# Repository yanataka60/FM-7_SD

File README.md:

# FM-7にSD-CARDからロード、セーブ機能

　FM-8、FM-7、FM-77シリーズでSD-CARDからロード、セーブ機能を実現するものです。

　対応できるBASICのバージョンは、FM-8はF-BASICV1.0(ROM-BASIC、DISK-VERSIONとも)、FM-7以降はF-BASICV3.0(ROM-BASIC、DISK-VERSIONとも)です。

　対応機種はFM-8からFM-77AV40SXまで全てのFMシリーズとなりますが、基板のRevsionにより対応範囲が異なります。

　Rev1.1とRev2.0の違いはコネクタのみです。

　Rev1.1はFM-7、FM-NEW7なら50Pinフラットケーブルで接続できますが、FM-77以降は外部拡張インタフェースの仕様が変更となっており、アンフェノール フルピッチへ変換するケーブルの自作が必要です。

　Rev2.0は32Pin拡張スロット仕様でFM-7以降全ての機種に接続できますが、純正の32Pinコネクタ(FCN-365P032-AU)は製造が終了してしまったため入手困難です。手持ちにある方は利用できますが、無い方はOMRON XC5A-3282-1が代替品として使えますが、加工が必要です。

　FM-8に繋げることが出来るのはRev3.0のみです。また、Rev3.0はFM-8、FM-7、FM-NEW7なら50Pinフラットケーブルで接続できますが、FM-77は外部拡張インタフェースの仕様が変更となっており、アンフェノール フルピッチへ変換するケーブルの自作が必要です。

|Revsion|対応機種|基板側コネクタ|本体側コネクタ|備考|
| ------------ | ------------ | ------------ | ------------ | ------------ |
|Rev1.1|FM-7、FM-NEW7|フラットケーブルコネクタ 50ピン|同左||
|Rev1.1|FM-77|フラットケーブルコネクタ 50ピン|アンフェノール フルピッチ50Pin|ケーブルの自作が必要|
|Rev1.1|FM-77AV|フラットケーブルコネクタ 50ピン|アンフェノール フルピッチ36Pin|ケーブルの自作が必要|
|Rev1.1|FM-77AV20以降|フラットケーブルコネクタ 50ピン|アンフェノール フルピッチ50Pin|ケーブルの自作が必要|
|Rev2.0|FM-7以降のすべて|32Pin拡張スロット||コネクタの加工が必要|
|Rev3.0|FM-8、FM-7、FM-NEW7|フラットケーブルコネクタ 50ピン|同左||
|Rev3.0|FM-77|フラットケーブルコネクタ 50ピン|アンフェノール フルピッチ50Pin|ケーブルの自作が必要|

### FM-8、FM-7、FM-77で使うときはBOOT-ROMの差替え有無を選択します。FM-77以降はFDD標準搭載なのでFDからFM-7_SD初期設定プログラムを走らせるものとしています。

　　1)BOOT-ROMを差し替える

　　2)BOOT-ROMを差し替えない。電源投入時又はRESET時に毎回CMTからFM-7_SD初期設定プログラムを読み込む(約15秒)

　　3)BOOT-ROMを差し替えない。電源投入時又はRESET時に毎回FDからFM-7_SD初期設定プログラムを走らせる。

　対応しているCMT形式は、FM-7がCMTで読み書きするベタCMT形式(拡張子bimとしています)です。T77からbimへの変換、bimからT77への変換にはツールを使って変換します。

　CMTからの読み込み実行に数分掛かっていたゲームも数十秒で実行できます。

　なお、Arduino、ROMへ書き込むための機器が別途必要となります。

## 対応できないもの
　BIOSのCMT読み書きルーチンをフックすることでSD-CARDへのアクセスを実現していますのでBIOSをコールせず独自ルーチンでCMTからLOADするソフト（ちゃっくんぽっぷ等）は対応できないのでLOAD出来ません。

　市販ソフトの多くが独自ルーチン、特殊フォーマットを使っているようです。

　bugfire2009さんのDumpListEditorにドロップしたときにファイルの大きさに比べて異様に小さなファイルしか解析できなかったり、(DAT)(unknown)と表示されるファイルが解析されるT77ファイルは独自ルーチン、特殊フォーマットを採用していると思います。

　市販ソフトがLOAD出来ればラッキーくらいに思って雑誌打ち込み系のLOADに活用してください。

## 回路図
### FM-7_SD Rev1.1基板
　KiCadフォルダ内Rev1.1フォルダのFM-7_SD_11.pdfを参照してください。

[回路図Rev1.1](https://github.com/yanataka60/FM-7_SD/blob/main/KiCad/Rev1.1/FM-7_SD_11.pdf)

### FM-7_SD Rev2.0基板
　KiCadフォルダ内Rev2.0フォルダのFM-7_SD_20.pdfを参照してください。

[回路図Rev2.0](https://github.com/yanataka60/FM-7_SD/blob/main/KiCad/Rev2.0/FM-7_SD_20.pdf)

### FM-7_SD Rev3.0基板
　KiCadフォルダ内Rev3.0フォルダのFM-7_SD_30.pdfを参照してください。

[回路図Rev3.0](https://github.com/yanataka60/FM-7_SD/blob/main/KiCad/Rev3.0/FM-7_SD_30.pdf)

## 部品
### FM-7_SD Rev1.1基板
|番号|品名|数量|備考|
| ------------ | ------------ | ------------ | ------------ |
|J1|2x25ボックスヘッダ|1|共立エレショップ JS-1200R-50など、秋月電子通商 PH-2x40RGなどのピンヘッダでも代用可(注5)|
||J4、J5のいずれか(注1)|||
|J4|Micro_SD_Card_Kit|1|秋月電子通商 AE-microSD-LLCNV (注2)|
|J5|MicroSD Card Adapter|1|Arduino等に使われる5V電源に対応したもの (注6)|
|U1|74LS04|1||
|U2|74LS30|1||
|U3|8255|1||
|U4|Arduino_Pro_Mini_5V|1|Atmega328版を使用 168版は不可。(注3)|
|U5|74LS00|1||
|C1 C3 C4 C6|積層セラミックコンデンサ 0.1uF|4||
|C2|電解コンデンサ 16v100uF|1||
||ピンヘッダ|2Pin分|Arduino_Pro_MiniにはA4、A5用のピンヘッダが付いていないため別途調達が必要です 秋月電子通商 PH-1x40SGなど|
||ピンソケット(任意)|26Pin分|Arduino_Pro_Miniを取り外し可能としたい場合に調達します 秋月電子通商 FHU-1x42SGなど|
||本体内BOOT-ROMを差し替える場合|||
||ROM 2716又は2732|1|AT28C16、M2732Aなど|
||2732変換基板又は24PinICソケット|1|2732を使った場合の切り替え用|
||3Pトグルスイッチ|1|2732を使った場合の切り替え用|

### FM-7_SD Rev2.0基板
|番号|品名|数量|備考|
| ------------ | ------------ | ------------ | ------------ |
|J1|FCN-365P032-AU又はOMRON XC5A-3282-1|1|(注4)|
||J4、J5のいずれか(注1)|||
|J4|Micro_SD_Card_Kit|1|秋月電子通商 AE-microSD-LLCNV (注2)|
|J5|MicroSD Card Adapter|1|Arduino等に使われる5V電源に対応したもの (注6)|
|U1|74LS04|1||
|U2|74LS30|1||
|U3|8255|1||
|U4|Arduino_Pro_Mini_5V|1|Atmega328版を使用 168版は不可。(注3)|
|U5|74LS00|1||
|C1 C3 C4 C6|積層セラミックコンデンサ 0.1uF|4||
|C2|電解コンデンサ 16v100uF|1||
||ピンヘッダ|2Pin分|Arduino_Pro_MiniにはA4、A5用のピンヘッダが付いていないため別途調達が必要です 秋月電子通商 PH-1x40SGなど|
||ピンソケット(任意)|26Pin分|Arduino_Pro_Miniを取り外し可能としたい場合に調達します 秋月電子通商 FHU-1x42SGなど|
||本体内BOOT-ROMを差し替える場合|||
||ROM 2716又は2732|1|AT28C16、M2732Aなど|
||2732変換基板又は24PinICソケット|1|2732を使った場合の切り替え用|
||3Pトグルスイッチ|1|2732を使った場合の切り替え用|

### FM-7_SD Rev3.0基板
|番号|品名|数量|備考|
| ------------ | ------------ | ------------ | ------------ |
|J1|2x25ボックスヘッダ|1|共立エレショップ JS-1200R-50など、秋月電子通商 PH-2x40RGなどのピンヘッダでも代用可(注5)|
||J4、J5のいずれか(注1)|||
|J4|Micro_SD_Card_Kit|1|秋月電子通商 AE-microSD-LLCNV (注2)|
|J5|MicroSD Card Adapter|1|Arduino等に使われる5V電源に対応したもの (注6)|
|U1 U7|74LS04|2||
|U2 U6|74LS30|2||
|U3|8255|1||
|U4|Arduino_Pro_Mini_5V|1|Atmega328版を使用 168版は不可。(注3)|
|U5|74LS00|1||
|C1 C3 C4 C5 C6 C7|積層セラミックコンデンサ 0.1uF|6||
|C2|電解コンデンサ 16v100uF|1||
||ピンヘッダ|2Pin分|Arduino_Pro_MiniにはA4、A5用のピンヘッダが付いていないため別途調達が必要です 秋月電子通商 PH-1x40SGなど|
||ピンソケット(任意)|26Pin分|Arduino_Pro_Miniを取り外し可能としたい場合に調達します 秋月電子通商 FHU-1x42SGなど|
||本体内BOOT-ROMを差し替える場合|||
||ROM 2716又は2732|1|AT28C16、M2732Aなど|
||2732変換基板又は24PinICソケット|1|2732を使った場合の切り替え用|
||3Pトグルスイッチ|1|2732を使った場合の切り替え用|

　　　注1)J4又はJ5のどちらかを選択して取り付けてください。

　　　注2)秋月電子通商　AE-microSD-LLCNVのJ1ジャンパはショートしてください。

　　　注3)Arduino Pro MiniはA4、A5ピンも使っています。

　　　注4)FCN-365P032-AUは入手困難、OMRON XC5A-3282-1は加工が必要

　　　　　OMRON XC5A-3282-1は、ハウジング内の凸型に出っ張ている部分を台形に近付けるように削ってください。

　　　注5)ピンヘッダで代用するときは、基板から若干浮かせてピンヘッダをハンダ付けするとフラットケーブをスムーズに抜き差しできます。

　　　注6)MicroSD Card Adapterを使う場合

　　　　　J5に取り付けます。

　　　　　MicroSD Card Adapterについているピンヘッダを除去してハンダ付けするのが一番確実ですが、J5の穴にMicroSD Card Adapterをぴったりと押しつけ、裏から多めにハンダを流し込むことでハンダ付けをする方法もあります。なお、この方法の時にはしっかりハンダ付けが出来たかテスターで導通を確認しておいた方が安心です。

ハンダ付けに自信のない方はJ4の秋月電子通商　AE-microSD-LLCNVをお使いください。AE-microSD-LLCNVならパワーLED、アクセスLEDが付いています。

## BOOT-ROMの差し替えを選択した場合
　FM-8、FM-7、FM-NEW7でBOOT-ROMの差し替えを選択した場合には、programフォルダ内bootromフォルダにある「FM-7_BOOTROM_SD.bin」を使いますが、Disk-Basicを使うか、使わないかでROMの差し替え方法が変わります。

　FM-8は「FM-7_BOOTROM_SD.bin」をbootrom_FM8フォルダにある「FM-8_BOOTROM_SD.bin」に読み替えてください。

#### 2023.2.17修正 DOS-MODEからの起動は出来ませんでした。運用方法は２通りとなります。

　1)FM-7_SDとCMTだけが使えればよい。(DISK-BASIC、DOS-MODEは使わない)

　　　元のBOOT-ROMを読み出す必要はありません。FM-7_BOOTROM_SD.binをROMライター(TL866II Plus等)を使ってROM 2716のアドレス$0000～$01FFに書き込んでBOOT-ROMのICソケットに装着します。

　2)FM-7_SDとCMTに加えてDISK-BASICは使いたい又は、FM-7_SD、CMT、DISK-BASIC、DOS-MODEのすべてを使いたい。

　　　ROM 2732の前半に元のBOOT-ROMの内容、後半の$0800～$09FFにFM-7_BOOTROM_SD.binとしたバイナリをROMライター(TL866II Plus等)を使って書き込みます。2732変換基板又は24PinICソケットの21Pinを曲げてスイッチで5VとGNDを切り替えられるようにしてBOOT-ROMのICソケットに装着します。

### FM-7 BOOT-ROMの場所

### FM-NEW7 BOOT-ROMの場所

### FM-8 BOOT-ROMの場所
電源ユニットの下です。

## SD-CARDアクセス初期設定プログラム
### BOOT-ROMを差し替えた場合
　programフォルダ内boot_iplフォルダの「@BOOT_IPL_FM-7.bin」をSD-CARDにコピーしてください。

　FM-8の場合は、boot_ipl_FM8フォルダ内の「@BOOT_IPL_FM-8.bin」をSD-CARDにコピーします。なお、「@BOOT_IPL_FM-7.bin」と「@BOOT_IPL_FM-8.bin」の両方がSD-CARDにコピーしてあっても大丈夫です。

　FM-7起動後に「EXEC &HFE02」(又は「EXEC -510」)を実行することでSD-CARDから「@BOOT_IPL_FM-7.bin」がテキストエリアの最初に読み込まれSD-CARDが使えるようBASICコマンドの追加、BIOSへのパッチあて、テキストエリアの再設定が行われます。

### BOOT-ROMを差し替えない場合
#### FDから起動
　DISKBASICフォルダのSDINIT_FM7.D77ディスクイメージをFDに書き込むか、SDINIT_FM7.binをFDに書き込んでください。

#### CMTから起動
　CMTLOADフォルダのSDINIT_FM7.wav(FM8は、SDINIT_FM8.wav)をCMTからロードして実行します。

## Arduinoプログラム
　Arduino IDEを使ってArduinoフォルダのFM-7_SDフォルダ内FM-7_SD.inoを書き込みます。FM-8も共通のプログラムを使用しています。

　SdFatライブラリを使用しているのでArduino IDEメニューのライブラリの管理からライブラリマネージャを立ち上げて「SdFat」をインストールしてください。

　「SdFat」で検索すれば見つかります。「SdFat」と「SdFat - Adafruit Fork」が見つかりますが「SdFat」のほうを使っています。

注)Arduinoを基板に直付けしていてもFM-7本体から外していれば書き込めます。

#### 電源が入ったFM-7本体とFM-7_SDを繋げたままArduinoを書き込む場合には、Arduinoに繋ぐシリアルコンバータから絶対に電源を供給しないでください。最悪FM-7本体が破壊される場合があります。

## 接続
　Rev1.1、Rev3.0をFM-8、FM-7、FM-NEW7で使う場合には本体後ろの50Pin拡張端子から50Pinフラットケーブルで接続します。

　50Pinフラットケーブルは、コネクタのボッチとケーブルの返しが両方上になる側のコネクタを本体に嵌めます。

　逆側のコネクタを本体に嵌めると一見嵌っているように見えてもケーブルの返しが基板に当たっていてちゃんと嵌っておらず接触不良を起こしていることがあります。

#### 悪い例です

　Rev1.1をFM-77以降、Rev3.0をFM-77で使う場合にはアンフェノール フルピッチへ変換するケーブルの自作が必要です。

　接続ピンは、はせりんさんのサイトが参考になります。

　http://haserin09.la.coocan.jp/difference.html

## SD-CARD
　出来れば8GB以下のSDカードを用意してください。

　ArduinoのSdFatライブラリは、SD規格(最大2GB)、SDHC規格(2GB～32GB)に対応していますが、SDXC規格(32GB～2TB)には対応していません。

　また、SDHC規格のSDカードであっても32GB、16GBは相性により動作しないものがあるようです。

　FAT16又はFAT32が認識できます。NTFSは認識できません。

　ルートに置かれた拡張子が「.BIM」のCMTベタ形式ファイルのみLOAD、SAVEできます。(以外のファイル、フォルダも表示されますが読み書き出来ません)

　ファイル名は拡張子を除いて32文字まで、ただし半角カタカナ、及び一部の記号はArduinoが認識しないので使えません。パソコンでファイル名を付けるときはアルファベット、数字および空白でファイル名をつけてください。

## T77ファイルの扱い方
　T77ファイルはそのまま使えません。

　Apolloさんが公開してくださっている「T77DEC」を使ってCMTベタ形式に変換して使います。

　http://retropc.net/apollo/

　変換例)T77DEC TEST.T77 -d[CR]

　を実行するとFULLDUMP.BINというファイルが出来上がるので拡張子を.bimに変えて使います。

　こんなバッチファイルを作ると便利です。

#### 2026.9.10) T77DECを使わずにBIMファイルが作成できるよう「T77toBIM」を作成しました。

　T77toBIMフォルダ中のT77toBIM.exeを実行します。

　変換例)T77toBIM TEST.T77 TEST.BIM[CR]

　を実行するとTEST.BIMというファイルが出来上がります。

#### bimファイルをT77に戻すにはBET2T77フォルダ内の「BET2T77.exe」を使います。

　「BET2T77.exe」を起動し、開いたウィンドウにbimファイルをドロップすればT77ファイルが作成されます。

#### 2026.3.23)「BET2T77.exeにドロップ出来ない」という症状の出る方がいるようですのでコンソール版「BET2T77_console.exe」を作成しました。

## 起動手順
### ROM-BASIC(BOOT-ROM差し替え済の場合)
　1　電源を入れます。

　2　この時点ではCMTが使えるROM-BASICが起動しています。

　3　「EXEC &HFE02」(又は「EXEC -510」)を実行します。

　4　「FM-7_SD READY OK!」と表示されたらSD-CARDにアクセスできます。BASICのフリーエリアは947Byte程減少します。

### DISK-BASIC
　1　電源を入れ、DISK-BASICを起動します。

　2　作成したFDの中にある「SDINIT」をロードし、実行します。

　　　LOADM"SDINIT"してからEXEC &H6000又はLOADM"SDINIT",,R

　3　「FM-7_SD READY OK!」と表示されたらSD-CARDにアクセスできます。

　4　LOADM"SDINIT",,RをSTARTUPとして保存し、AUTOUTYで自動実行を設定すれば手間が省けます。

　5　SDからLOAD、SAVEする場合にはファイルデスクリプタ「CAS0:」が必ず必要になります。

(2026.10.14追加)CMTからロードできるようにWAVファイルを置きました。

　LOADM"CAS0:SDINIT"でCMTよりロードした後にFDに保存してください。

　(FM7)SAVEM"SDINIT",&H6000,&H6498,&H6000

　(FM8)SAVEM"SDINIT",&H6000,&H6418,&H6000

## 使い方
　BASICから以下のコマンドが使えます。
### CMT[CR]
CMTを使いたい時に実行します。

BIOSのフックを元に戻してCMTが使えるようにします。ただし、SD-CARDアクセス用のプログラムは常駐したまま残っていますのでBASICのフリーエリアは減少したままです。

### SDON[CR]
CMTコマンドで戻してしまったBIOSのフックをSD-CARD用にフックし直します。

CMTコマンドと合わせて使えばCMTから読み込んでSD-CARDに保存することができます。

### SETL "DOSファイル名"[CR]
指定したDOSファイル名のファイルをSD-CARDからLOAD出来るようにセットします。ファイル名の前には必ずダブルコーテーションをつけてください。後ろのダブルコーテーションは有っても無くても構いません。

ファイル名の最後の「.bim」は有っても無くても構いません。

SETLを実行することでカセットテープをセットして読み込む準備をしたことになります。

### LOAD
F-BASICのLOADコマンドと同じ使い方になります。

#### 例)
　　LOAD[CR]

　　LOAD "TEST"[CR]

　　LOAD "CAS0:TEST"[CR]

　　LOAD "TEST",R[CR]

ROM-BASICの場合には、ファイルデスクリプタ「CAS0:」は有っても無くても構いません。DISK-BASICの場合にSDからLOADするには必ず必要です。

カセットテープと同じようにLOAD命令等で読み込みが行われる度にDOSファイル名で指定したファイルに保存されているプログラム又はデータが先頭から一つずつ読み込まれます。

カセットデッキのように巻き戻しは無いので戻りたい時にはもう一度SETLコマンドを実行すれば先頭のプログラム又はデータに戻ります。

### LOADM
F-BASICのLOADMコマンドと同じ使い方です。

### SETS "DOSファイル名"[CR]
指定したDOSファイル名のファイルをSD-CARDへSAVE出来るようにセットします。ファイル名の前には必ずダブルコーテーションをつけてください。後ろのダブルコーテーションは有っても無くても構いません。

ファイル名の最後の「.bim」は有っても無くても構いません。

指定したDOSファイル名のファイルがSD-ACRDに存在しない場合は新たに作成され、存在する場合にはそのファイルの続きに追記されます。

SETSを実行することでカセットテープをセットして書き込む準備をしたことになります。

なお、SETSを実行せずにSAVE、SAVEMコマンドを実行すると「DEFAULT.bim」というDOSファイル名のファイルに自動的に書き込まれます。

「DEFAULT.bim」でなく好きなDOSファイル名のファイルに書き込みたい時には事前にSETSコマンドを実行してください。

### SAVE
F-BASICのSAVEコマンドと同じ使い方になります。

#### 例)
　　SAVE "TEST"[CR]

　　SAVE "CAS0:TEST"[CR]

　　SAVE "TEST",A[CR]

　　SAVE "TEST",P[CR]

ROM-BASICの場合には、ファイルデスクリプタ「CAS0:」は有っても無くても構いません。DISK-BASICの場合にSDへSAVEするには必ず必要です。

### SAVEM
F-BASICのSAVEMコマンドと同じ使い方です。

### SDIR[CR] 又は SDIR "文字列"[CR]

文字列を指定するときは必ずダブルコーテーションをつけてください。後ろのダブルコーテーションは有っても無くても構いません。

文字列を入力せずにSDIR[CR]のみ入力するとSD-CARDルートディレクトリにあるファイルの一覧を表示します。

文字列を付けて入力すればSD-CARDルートディレクトリにあるその文字列から始まるファイルの一覧を表示します。

10件表示したところで指示待ちになるので打ち切るならESCを入力すると打ち切られ、Bキーで前の10件に戻ります。それ以外のキーで次の10件を表示します。

　行頭に0から9の数字を付加して表示してあるのでSETLしたいファイルの頭についている数字を入力するとSETLコマンドが実行されます。

　表示される順番は、登録順となりファイル名アルファベッド順などのソートした順で表示することはできません。

#### 例)
　　SDIR[CR]

　　SDIR "P"[CR]

### 操作上の注意
　~~「SD-CARD INITIALIZE ERROR」と表示されたときは、SD-CARDをいったん抜き再挿入したうえでArduinoをリセットしてください。~~

　~~SD-CARDにアクセスしていない時に電源が入ったままで SD-CARDを抜いた後、再挿入しSD-CARDにアクセスすると「SD-CARD INITIALIZE ERROR」となる場合があります。再挿入した場合にはSD-CARDにアクセスする前にArduinoを必ずリセットしてください。~~

　~~SD-CARDの抜き差しは電源を切った状態で行うほうがより確実です。~~

　(2024.3.12) SD-CARDにアクセスしていない時に電源が入ったままでSD-CARDを抜くと再度SD-CARDを挿入してもSD-CARDにアクセスできない問題を解消しました。(Arduinoを最新版に書き換えてください)

　再度SD-CARDを挿入した後、SDIR、SETL、SETS等でSD-CARDに3回ほどアクセスすれば復旧します。

　LOAD、LOADM、SAVE、SAVEMでは復旧しません。

## EXAS-FMコンパイラ起動プログラム
　月刊I/O '84/4月号に掲載されたEXAS-FMコンパイラをFM-7_SDから起動できるようにする起動プログラムです。

### EXAS-FMコンパイラSD起動用ファイルの作成
　まず、EXAS-FMコンパイラ本体のバイナリファイルを掲載のダンプリストどおりに打ち込みます。

　記事では「実際にROMに書き込むときには、8FFAの6バイトに次の物を入れ、8FFA-EFF9を書き込んでください。」となっています。この6バイトは付いていても付いていなくてもどちらでも構いません。

　バイナリエディタ等でEXAS-FM_BOOTフォルダにある「EXAS-FM_BOOT.bim」の後ろにEXAS-FMコンパイラ本体をくっつけ「EXAS-FM.bim」というファイル名で保存し、SD-CARDにコピーしてください。

　出来上がったEXAS-FMコンパイラSD起動用ファイルのサイズは、6バイトを付加していれば25304Byte、いなければ25298Byteとなるはずです。

### 起動方法
　FM-7を起動し、「EXEC&HFE02」を実行します。

　「clear,&h6FFF」でEXAS-FMコンパイラSD起動用プログラムの領域を確保します。

　「sdir」で「EXAS-FM」を選択します。

　「loadm」「exec&H7000」又は「loadm"EXAS-FM",,R」でEXAS-FMコンパイラが裏RAMに転送、実行されます。

　コンパイルでエラー等が発生し、ソースプログラムを修正したのちに再度コンパイルする場合には次の２通りの方法があります。

　　１　FM-7をSDモードで起動している場合には、「EXEC&HFFE8」でEXAS-FMコンパイラを起動できます。

　　２　DISK-BASICから起動してFM-7_SDを使っている場合には、「sdir」で「EXAS-FM」を選択後、「loadm」「exec&H7000」又は「loadm"EXAS-FM",,R」を再度実行してください。ただし、裏RAMにEXAS-FMコンパイラが既に転送されていますのでSDからEXAS-FMコンパイラの読み込みは行われずに起動します。

## 簡略版@BOOT_IPL_FM-7.bin、簡略版@BOOT_IPL_FM-8.bin
　ひぽぽ様より月刊I/O '82/2月号に掲載された「ALL CAST STAR TREK」がSDから読込めはしたものの実行するとOut Of Memoryで止まってしまうという情報を頂きました。

　記事中にも「メモリをフルに使用しており」との記載があり、フリーエリアぎりぎりまで使用しているため、@BOOT_IPL_FM-x.binの常駐によるフリーエリアの減少によりOut Of Memoryになってしまうようです。

　しかし、SDからLOADは出来ており、実行時に変数を割り当てた段階でOut Of Memoryになるのであればちょっと頑張れば実行できる可能性がありそうです。

　そこで@BOOT_IPL_FM-x.binで追加するコマンドを必要最低限の「SDIR」「SETS」のみとした簡略版を作成しました。

　今のところ「ALL CAST STAR TREK」も無事動いているようです。

　通常版との違いは以下のとおりですが、通常の運用にも困らないと思います。

　・CMT、SDON、SETLコマンドが使えない。

　・エラーメッセージ等のメッセージを簡略化。

　・追加CMDテーブルがギリギリサイズ。

### 使用方法
　EXTRA-programフォルダにある「@BOOT_IPL_FM-7.bin」「@BOOT_IPL_FM-8.bin」をSDカードにコピーし、既存の「@BOOT_IPL_FM-7.bin」「@BOOT_IPL_FM-8.bin」を上書きしてください。

## プログラム・ポシェット No.6掲載「PF-X」をFM-7_SDで使えるようにするIPSパッチ
　ひぽぽ様よりプログラム・ポシェット No.6掲載「PF-X」をFM-7_SDで使いたいとの要望がありました。

　「PF-X」もBASICにコマンドを追加することでPCGを実現しており、FM-7_SDのコマンド追加を上書きしてしまうため、FM-7_SDが正常に動作しなくなってしまいます。

　そこで「PF-X」の初期化ルーチンに手を入れ、FM-7_SDと両立できるIPSパッチを作成しました。

### PF-Xの準備
　PF-Xへのパッチ当てにあたり、PF-Xのバイナリファイルを用意してください。

　プログラム・ポシェット掲載のBASICプログラムは、DATA文を読み込み&H4000から機械語プログラム(&H4000～&H42CF 720Byte)を書き込み、エラーが無ければEXEC &H4000でPF-Xが使えるようになります。

　BASICプログラムのDATA文を見ながらバイナリファイル(&H4000～&H42CF 720Byte)が作成できる方はPF-X.bin等のファイル名を付けて保存します。

　そうでない方は、エミュレータ又は実機でPF-XのBASICプログラムを実行し、「READY !!」と表示された後に「SAVEM "PF-X",&H4000,&H42CF,&H4000」を実行してCMTに保存します。

　保存した機械語をDumpListEditor等を使い、ヘッダ等の無いバイナリファイル(&H4000～&H42CF 720Byte)として保存します。

### パッチ当て
　作成したPF-XのバイナリファイルにWinIPS等を使い、EXTRA-programフォルダにある「PF-X_SD.ips」のパッチを当ててください。

　「PF-X_SD.BIN」(2287Byte)というファイルが出来上がりますので「PF-X_SD.bim」にリネームしてSDカードにコピーします。

### PF-X_SDの実行
　SDIR等で「PF-X_SD」を選択し、LOADMで読み込み、EXEC &H4000で実行します。

　「PF-X READY OK!」と表示されれば終了です。

　FM-7_SDとしては、簡略版@BOOT_IPL_FM-7.binで起動しても通常版@BOOT_IPL_FM-7.binの機能が使えるようになってます。

　PF-Xの使い方は、プログラム・ポシェット No.6を参照願います。

## 謝辞
　基板の作成に当たり以下のデータを使わせていただきました。ありがとうございます。

　Arduino Pro Mini

　　https://github.com/g200kg/kicad-lib-arduino

　AE-microSD-LLCNV

　　https://github.com/kuninet/PC-8001-SD-8kRAM

　Apollo様、公開していただいているソフトを使わせていただきました。ありがとうございます。

　はせりん様のサイトにあるインタフェース仕様表が大変参考になりました。ありがとうございます。

　　http://haserin09.la.coocan.jp/difference.html

　AIGOU Yoshiaki様に少しの加工でOMRON XC5A-3282-1がFCN-365P032-AUの代替に使えると教えていただきました。ありがとうございます。

## 追記
2023.2.11 @BOOT_IPL_FM-7.binをリロケータブルに修正

2023.2.13 FDからFM-7_SDの初期設定を行うプログラムを追加

　　　　　FM-77、FM-77AVにおける動作状況を追記しました。

2023.2.15 CMTから読み込む方法も追加しました。

2023.2.17 DOS-MODEからの起動は出来ませんでした。BOOT-ROMの差し替え方は２通りとなります。

2023.2.18 50Pinフラットケーブルの嵌め方を追記しました。

2023.2.21 機種、コネクタの違いから基板3種(Rev1.1、Rev2.0、Rev3.0)を用意したため、Documentを全面修正しました。

2023.4.12 EXAS-FMコンパイラ起動用プログラムを追加しました。

2024.1.15 SDカードは8GB以下が望ましいことを追記。

2024.3.12 電源が入ったままでSD-CARDを抜くと再度SD-CARDを挿入してもSD-CARDにアクセスできない問題を解消した。

2024.5. 2 簡略版@BOOT_IPL_FM-7.bin、簡略版@BOOT_IPL_FM-8.binを公開しました。

　　　　　プログラム・ポシェット No.6掲載「PF-X」をFM-7_SDで使えるようにするIPSパッチを公開しました。

2025.1.29 コネクタの記述を修正しました。

2026.3.23 コンソール版「BET2T77_console.exe」を追加。

2026.9.10 独自にT77からBIMファイルに変換できるようT77toBIM.exeを追加。

2026.10.14 DISKBASICからSDINITを読み込むためにWAVファイルも用意しました。

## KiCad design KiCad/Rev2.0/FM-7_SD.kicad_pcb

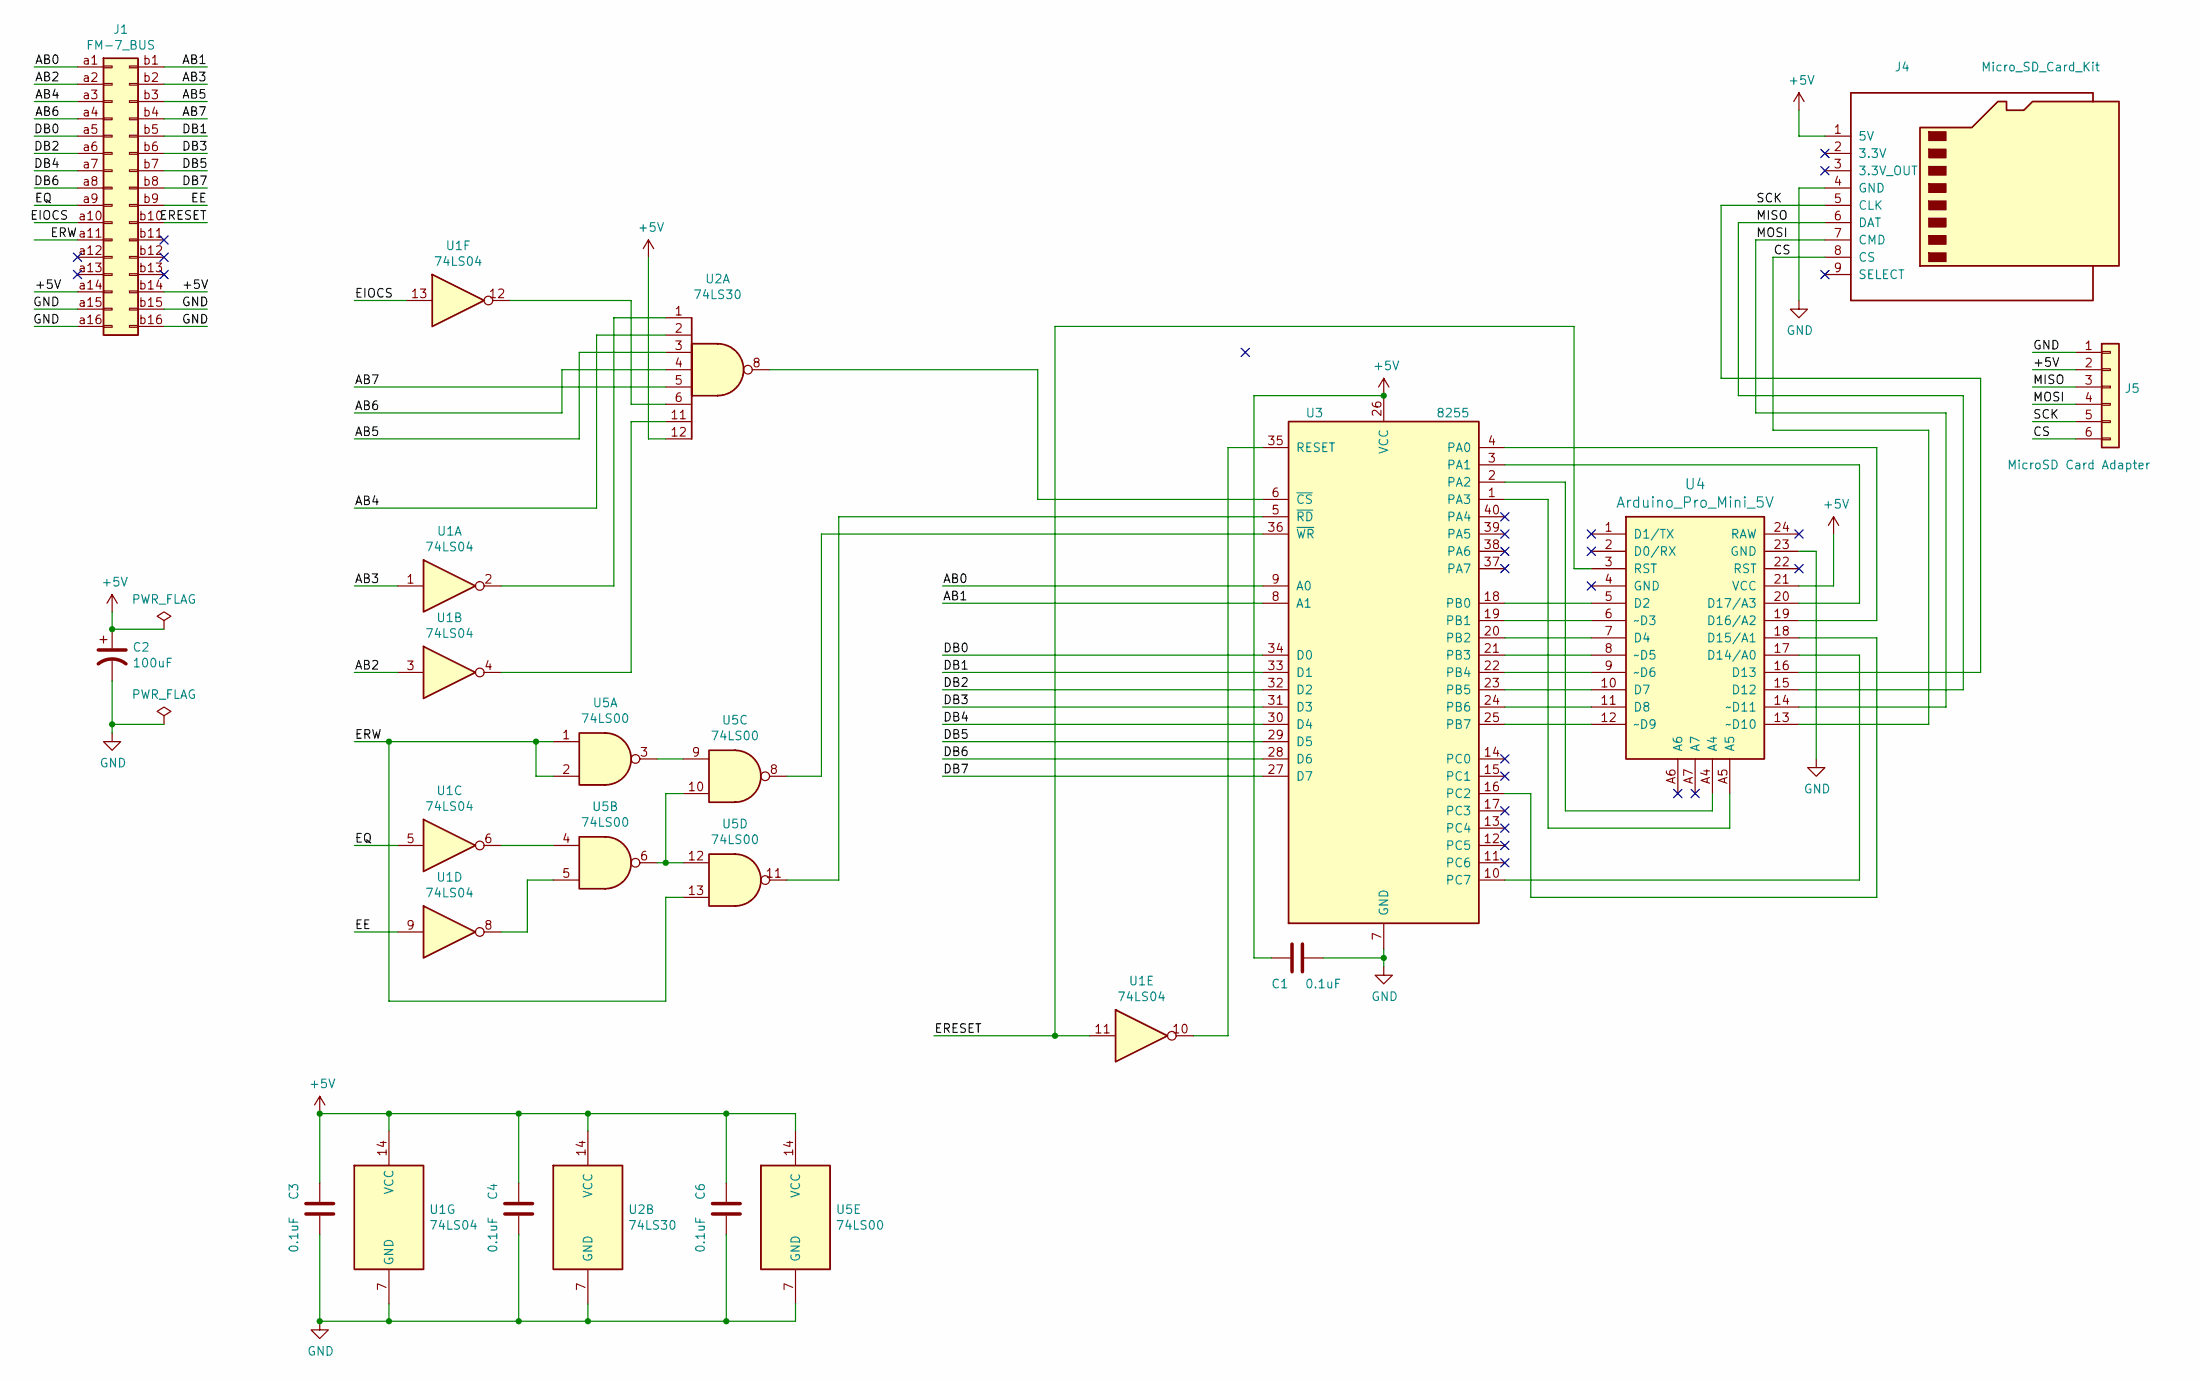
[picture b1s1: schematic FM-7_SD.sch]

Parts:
C1, C3, C4, C6: 0.1uF; C_Rect_L4.0mm_W2.5mm_P2.50mm
C2: 100uF; CP_Radial_D5.0mm_P2.50mm
J1: FM-7_BUS; DIN41612_B2_2x16_Female_Vertical_THT
J4: Micro_SD_Card_Kit; AE-microSD-LLCNV
J5: MicroSD Card Adapter; PinSocket_1x06_P2.54mm_Vertical
U1: 74LS04; DIP-14_W7.62mm_LongPads
U2: 74LS30; DIP-14_W7.62mm_LongPads
U3: 8255; DIP-40_W15.24mm_LongPads
U4: Arduino_Pro_Mini_5V; Arduino_Pro_Mini
U5: 74LS00; DIP-14_W7.62mm_LongPads

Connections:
+5V: C1.1, C2.1, C3.1, C4.1, C6.1, J1.a14, J1.b14, J4.1 (5V), J5.2, U1.14 (VCC), U2.12, U2.14 (VCC), U3.26 (VCC), U4.21 (VCC), U5.14 (VCC)
/AB0: J1.a1, U3.9 (A0)
/AB1: J1.b1, U3.8 (A1)
/AB2: J1.a2, U1.3
/AB3: J1.b2, U1.1
/AB4: J1.a3, U2.2
/AB5: J1.b3, U2.3
/AB6: J1.a4, U2.4
/AB7: J1.b4, U2.5
/CS: J4.8 (CS), J5.6, U4.13 (~~D10)
/DB0: J1.a5, U3.34 (D0)
/DB1: J1.b5, U3.33 (D1)
/DB2: J1.a6, U3.32 (D2)
/DB3: J1.b6, U3.31 (D3)
/DB4: J1.a7, U3.30 (D4)
/DB5: J1.b7, U3.29 (D5)
/DB6: J1.a8, U3.28 (D6)
/DB7: J1.b8, U3.27 (D7)
/EE: J1.b9, U1.9
/EIOCS: J1.a10, U1.13
/EQ: J1.a9, U1.5
/ERESET: J1.b10, U1.11, U4.3 (RST)
/ERW: J1.a11, U5.1, U5.2, U5.13
/MISO: J4.6 (DAT), J5.3, U4.15 (D12)
/MOSI: J4.7 (CMD), J5.4, U4.14 (~~D11)
/SCK: J4.5 (CLK), J5.5, U4.16 (D13)
GND: C1.2, C2.2, C3.2, C4.2, C6.2, J1.a15, J1.a16, J1.b15, J1.b16, J4.4 (GND), J5.1, U1.7 (GND), U2.7 (GND), U3.7 (GND), U4.23 (GND), U5.7 (GND)
unnamed: U1.2, U2.1
unnamed: U1.4, U2.11
unnamed: U1.6, U5.4
unnamed: U1.8, U5.5
unnamed: U1.10, U3.35 (RESET)
unnamed: U1.12, U2.6
unnamed: U2.8, U3.6 (~CS~)
unnamed: U3.1 (PA3), U4.A5
unnamed: U3.2 (PA2), U4.A4
unnamed: U3.3 (PA1), U4.20 (D17/A3)
unnamed: U3.4 (PA0), U4.19 (D16/A2)
unnamed: U3.5 (~RD~), U5.11
unnamed: U3.10 (PC7), U4.17 (D14/A0)
unnamed: U3.16 (PC2), U4.18 (D15/A1)
unnamed: U3.18 (PB0), U4.5 (D2)
unnamed: U3.19 (PB1), U4.6 (~~D3)
unnamed: U3.20 (PB2), U4.7 (D4)
unnamed: U3.21 (PB3), U4.8 (~~D5)
unnamed: U3.22 (PB4), U4.9 (~~D6)
unnamed: U3.23 (PB5), U4.10 (D7)
unnamed: U3.24 (PB6), U4.11 (D8)
unnamed: U3.25 (PB7), U4.12 (~~D9)
unnamed: U3.36 (~WR~), U5.8
unnamed: U5.3, U5.9
unnamed: U5.6, U5.10, U5.12

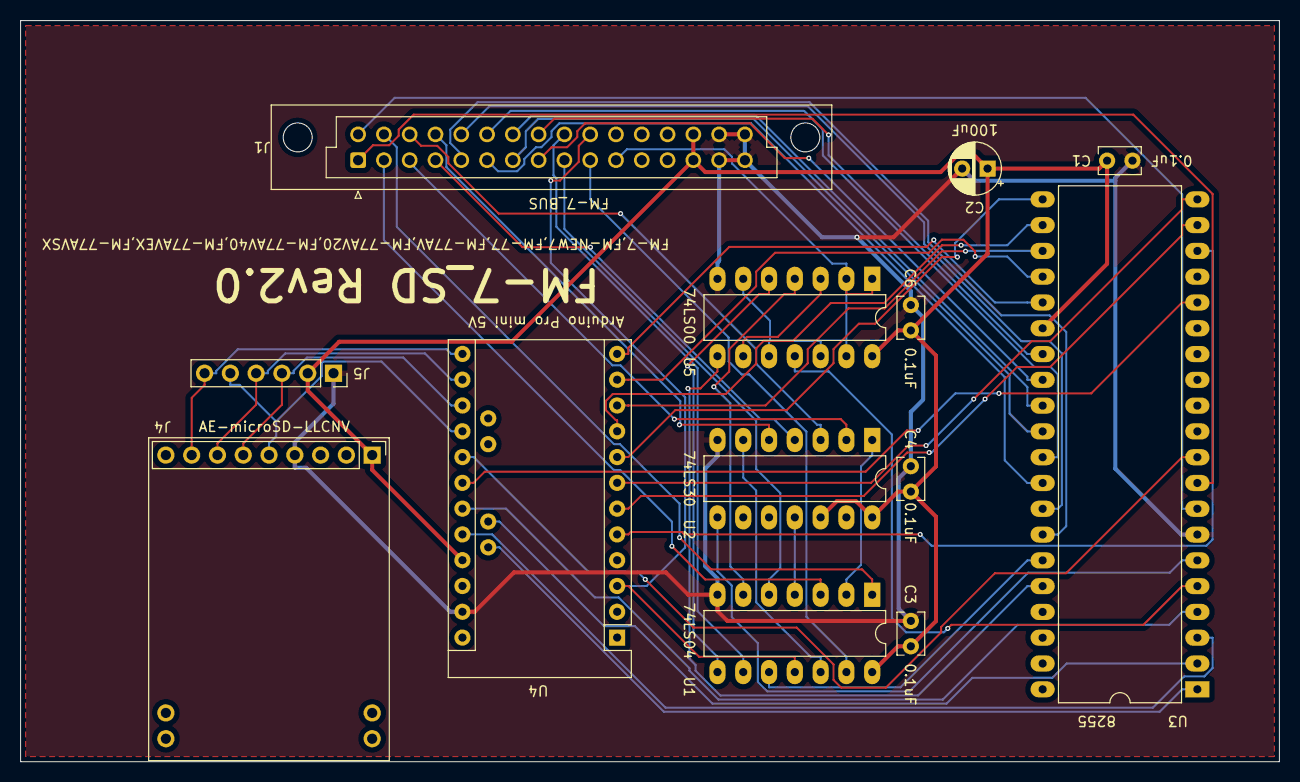
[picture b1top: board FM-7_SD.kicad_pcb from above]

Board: 2 copper layers, 124.0 x 73.0 mm, 13 parts (0 on the bottom side), 52 nets.
